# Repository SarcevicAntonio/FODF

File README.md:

# Fundamentals of Digital Fabrication

This repo is the documentation of my Fundamentals of Digital Fabrication class, where we learned about the basics of 2D and 3D Design, Laser Cutting, 3D Printing, Electronics Productions and Design and Embedded Programming with Input and Output Devices. We then had to use all these skills in a Final Project.

[Read more in the documentation of the class.](https://sarcevicantonio.github.io/FODF/)

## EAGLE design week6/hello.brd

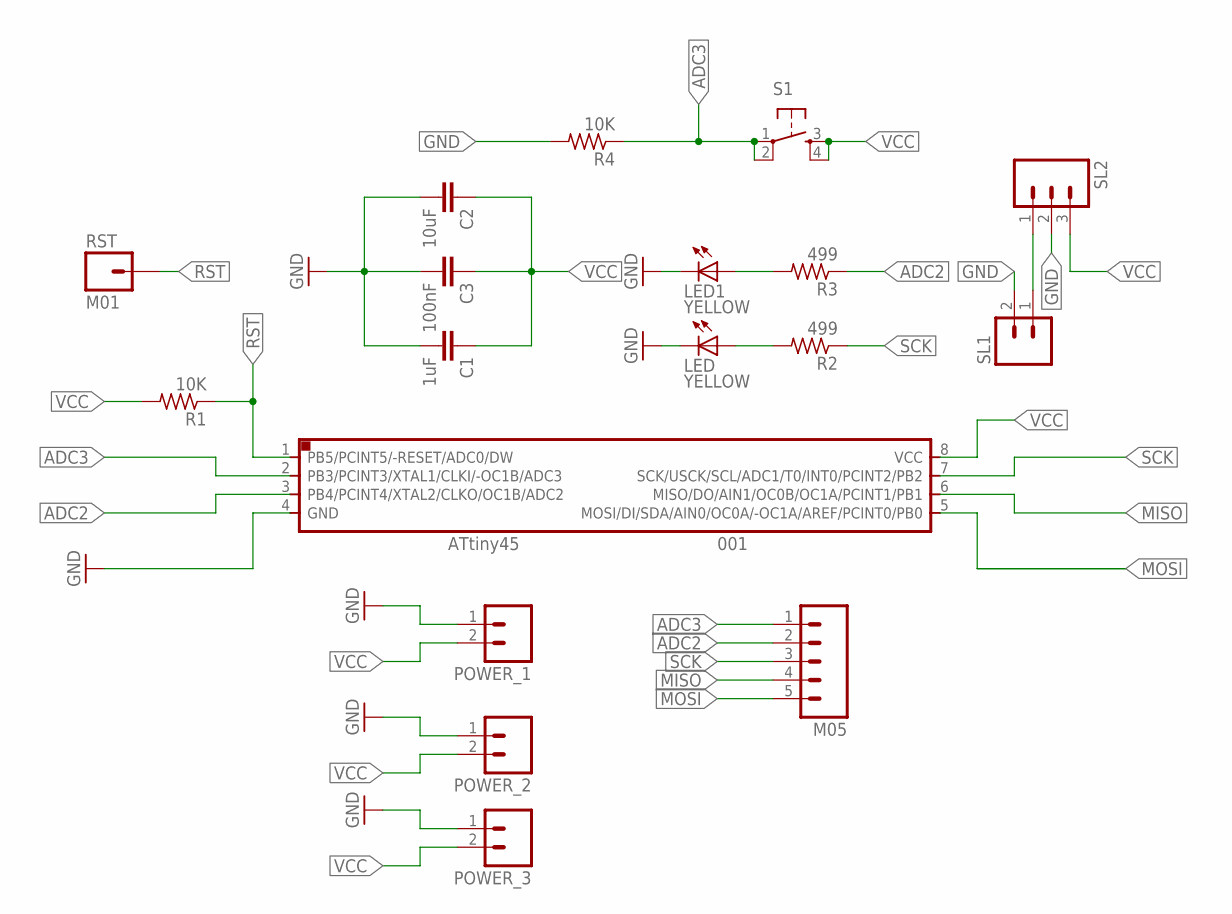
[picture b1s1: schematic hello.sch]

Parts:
001: ATTINY45SI; SOIC8
C1: 1uF; 1206
C2: 10uF; 1206
C3: 100nF; 1206
LED, LED1: YELLOW; LED1206FAB
M05: M05; 05P
POWER_1, POWER_2, POWER_3: M02; 02P
R1, R4: 10K; R1206FAB
R2, R3: 499; R1206FAB
RST: M01; 1X01_LONGPAD
S1: 6MM_SWITCH6MM_SWITCH; 6MM_SWITCH
SL1: M02; 02P
SL2: M03; 03P

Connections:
ADC2: 001.3 (PB4/PCINT4/XTAL2/CLKO/OC1B/ADC2), M05.2, R3.1
ADC3: 001.2 (PB3/PCINT3/XTAL1/CLKI/-OC1B/ADC3), M05.1, R4.1, S1.1, S1.2 (P1)
GND: 001.4 (GND), C1.2, C2.2, C3.2, LED.2 (C), LED1.2 (C), POWER_1.1, POWER_2.1, POWER_3.1, R4.2, SL1.2, SL2.2
MISO: 001.6 (MISO/DO/AIN1/OC0B/OC1A/PCINT1/PB1), M05.4
MOSI: 001.5 (MOSI/DI/SDA/AIN0/OC0A/-OC1A/AREF/PCINT0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), M05.5
unnamed: LED1.1 (A), R3.2
unnamed: SL1.1, SL2.1
unnamed: LED.1 (A), R2.2
RST: 001.1 (PB5/PCINT5/-RESET/ADC0/DW), R1.1, RST.1
SCK: 001.7 (SCK/USCK/SCL/ADC1/T0/INT0/PCINT2/PB2), M05.3, R2.1
VCC: 001.8 (VCC), C1.1, C2.1, C3.1, POWER_1.2, POWER_2.2, POWER_3.2, R1.2, S1.3 (S), S1.4 (S1), SL2.3

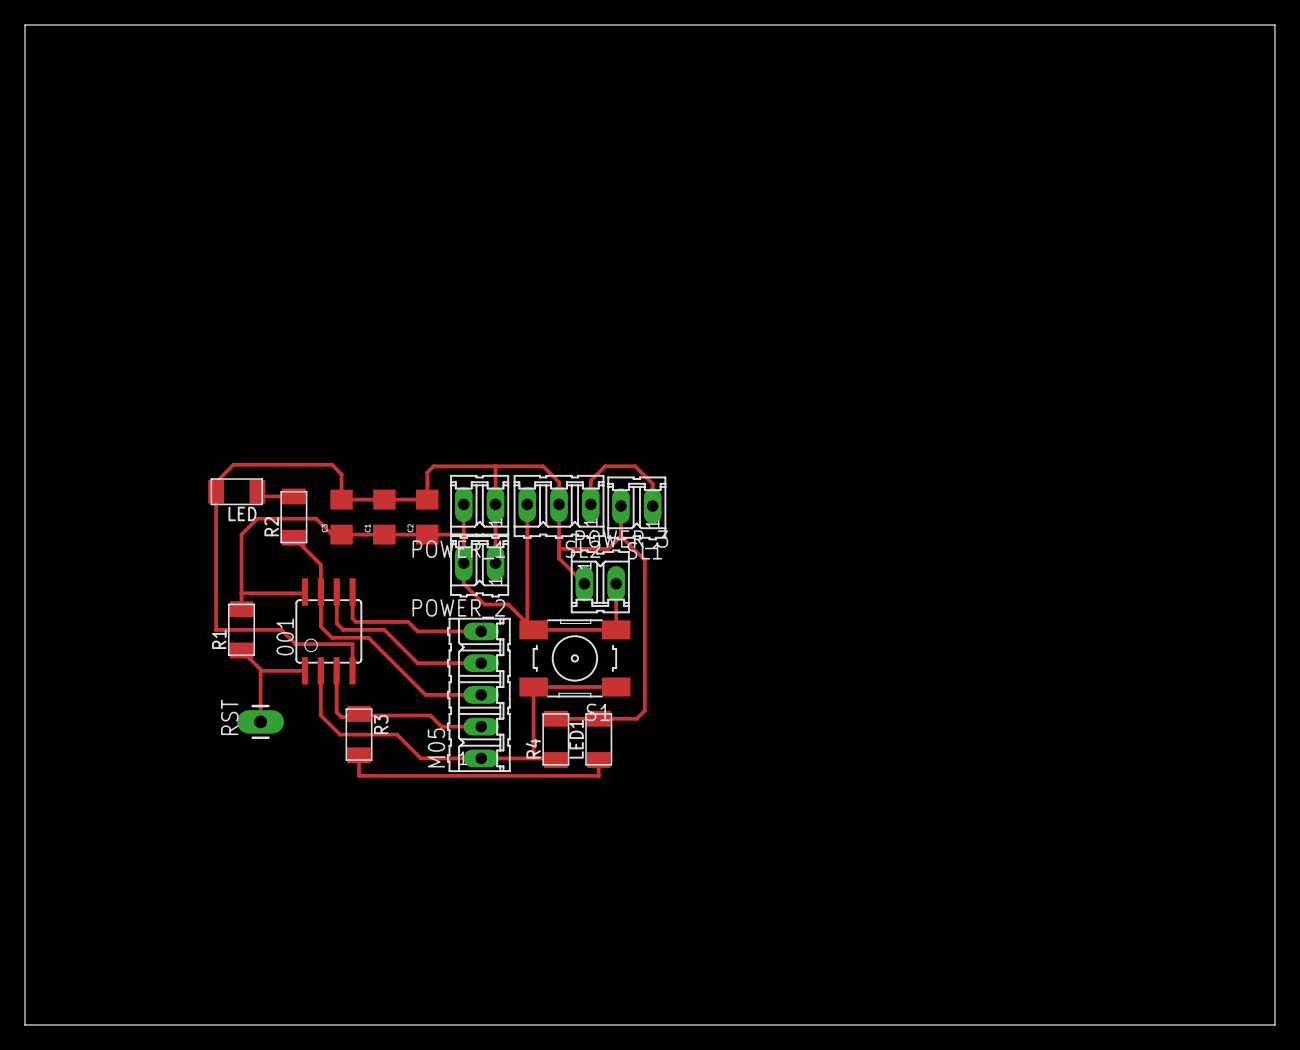
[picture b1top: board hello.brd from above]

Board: 2 copper layers, 100.0 x 80.0 mm, 18 parts (0 on the bottom side), 11 nets.

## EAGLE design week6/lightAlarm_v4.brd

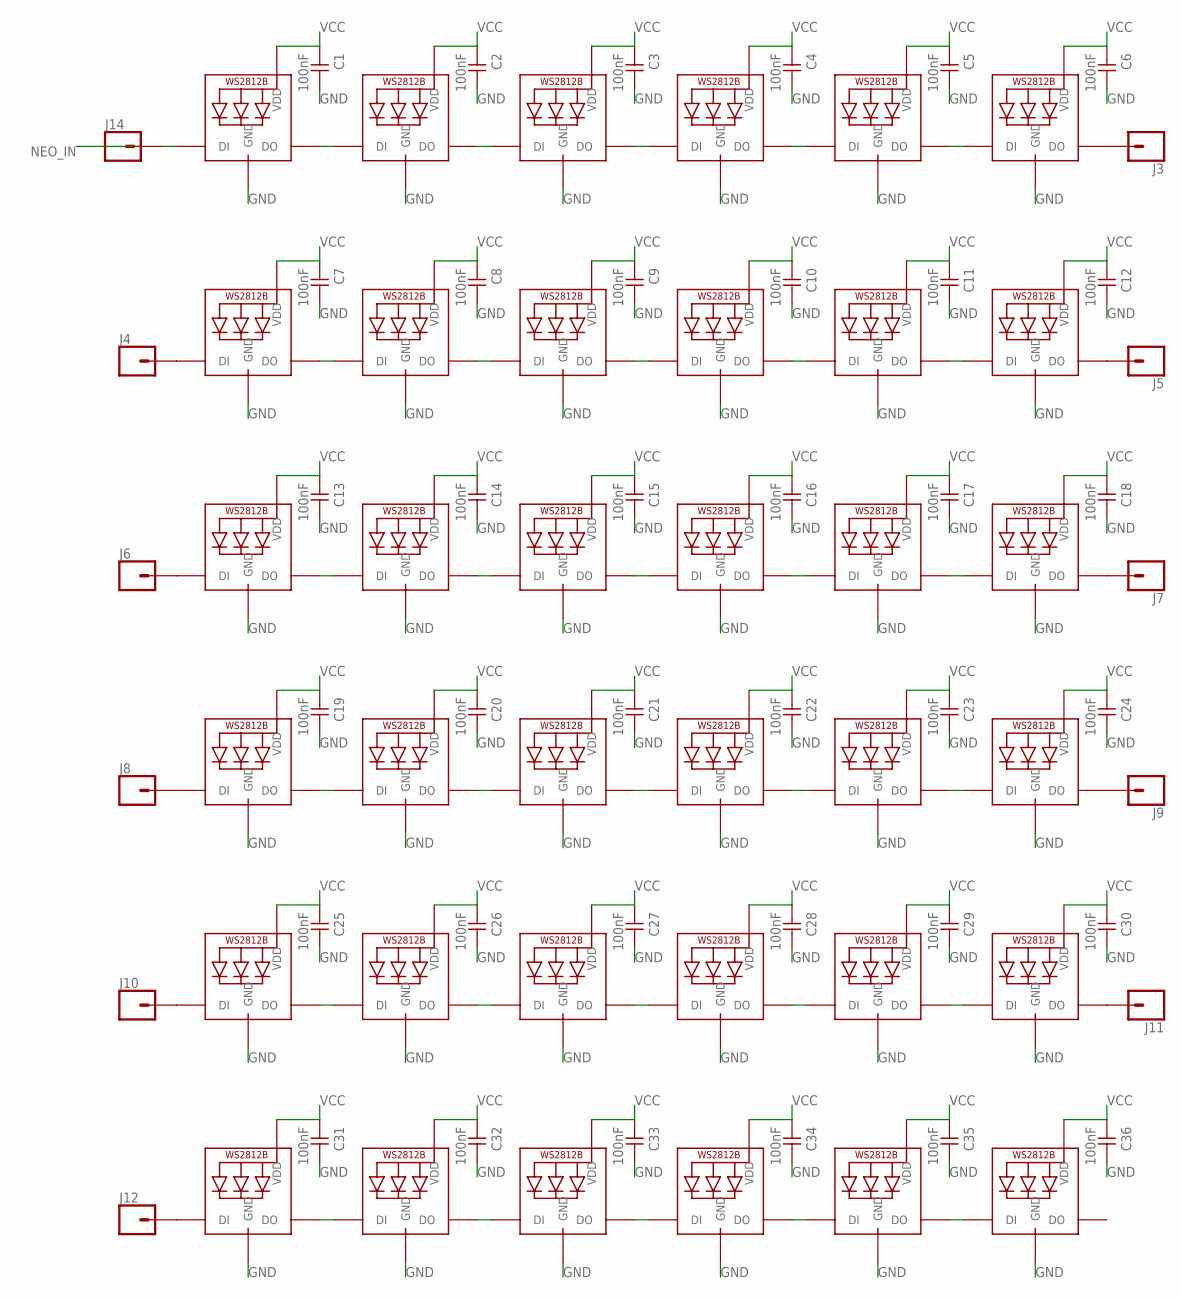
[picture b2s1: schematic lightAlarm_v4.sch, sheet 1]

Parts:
C1, C2, C3, C4, C5, C6, C7, C8, C9, C10, C11, C12, C13, C14, C15, C16, C17, C18, C19, C20, C21, C22, C23, C24, C25, C26, C27, C28, C29, C30, C31, C32, C33, C34, C35, C36: 100nF; 1206
J3, J4, J5, J6, J7, J8, J9, J10, J11, J12, J14: CONN_01PTH_LONGPAD; 1X01_LONGPAD
LED1, LED2, LED3, LED4, LED5, LED6, LED7, LED8, LED9, LED10, LED11, LED12, LED13, LED14, LED15, LED16, LED17, LED18, LED19, LED20, LED21, LED22, LED23, LED24, LED25, LED26, LED27, LED28, LED29, LED30, LED31, LED32, LED33, LED34, LED35, LED36: WS2812B5050; WS2812B

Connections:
GND: C1.2, C2.2, C3.2, C4.2, C5.2, C6.2, C7.2, C8.2, C9.2, C10.2, C11.2, C12.2, C13.2, C14.2, C15.2, C16.2, C17.2, C18.2, C19.2, C20.2, C21.2, C22.2, C23.2, C24.2, C25.2, C26.2, C27.2, C28.2, C29.2, C30.2, C31.2, C32.2, C33.2, C34.2, C35.2, C36.2, LED1.3-GND (GND), LED2.3-GND (GND), LED3.3-GND (GND), LED4.3-GND (GND), LED5.3-GND (GND), LED6.3-GND (GND), LED7.3-GND (GND), LED8.3-GND (GND), LED9.3-GND (GND), LED10.3-GND (GND), LED11.3-GND (GND), LED12.3-GND (GND), LED13.3-GND (GND), LED14.3-GND (GND), LED15.3-GND (GND), LED16.3-GND (GND), LED17.3-GND (GND), LED18.3-GND (GND), LED19.3-GND (GND), LED20.3-GND (GND), LED21.3-GND (GND), LED22.3-GND (GND), LED23.3-GND (GND), LED24.3-GND (GND), LED25.3-GND (GND), LED26.3-GND (GND), LED27.3-GND (GND), LED28.3-GND (GND), LED29.3-GND (GND), LED30.3-GND (GND), LED31.3-GND (GND), LED32.3-GND (GND), LED33.3-GND (GND), LED34.3-GND (GND), LED35.3-GND (GND), LED36.3-GND (GND); also elsewhere on the board
unnamed: LED1.2-DOUT (DO), LED2.4-DIN (DI)
unnamed: LED3.2-DOUT (DO), LED4.4-DIN (DI)
unnamed: LED2.2-DOUT (DO), LED3.4-DIN (DI)
unnamed: LED5.2-DOUT (DO), LED6.4-DIN (DI)
unnamed: LED4.2-DOUT (DO), LED5.4-DIN (DI)
unnamed: LED7.2-DOUT (DO), LED8.4-DIN (DI)
unnamed: LED9.2-DOUT (DO), LED10.4-DIN (DI)
unnamed: LED8.2-DOUT (DO), LED9.4-DIN (DI)
unnamed: LED11.2-DOUT (DO), LED12.4-DIN (DI)
unnamed: LED10.2-DOUT (DO), LED11.4-DIN (DI)
unnamed: LED13.2-DOUT (DO), LED14.4-DIN (DI)
unnamed: LED15.2-DOUT (DO), LED16.4-DIN (DI)
unnamed: LED14.2-DOUT (DO), LED15.4-DIN (DI)
unnamed: LED17.2-DOUT (DO), LED18.4-DIN (DI)
unnamed: LED16.2-DOUT (DO), LED17.4-DIN (DI)
unnamed: LED19.2-DOUT (DO), LED20.4-DIN (DI)
unnamed: LED21.2-DOUT (DO), LED22.4-DIN (DI)
unnamed: LED20.2-DOUT (DO), LED21.4-DIN (DI)
unnamed: LED23.2-DOUT (DO), LED24.4-DIN (DI)
unnamed: LED22.2-DOUT (DO), LED23.4-DIN (DI)
unnamed: LED25.2-DOUT (DO), LED26.4-DIN (DI)
unnamed: LED27.2-DOUT (DO), LED28.4-DIN (DI)
unnamed: LED26.2-DOUT (DO), LED27.4-DIN (DI)
unnamed: LED29.2-DOUT (DO), LED30.4-DIN (DI)
unnamed: LED28.2-DOUT (DO), LED29.4-DIN (DI)
unnamed: LED31.2-DOUT (DO), LED32.4-DIN (DI)
unnamed: LED33.2-DOUT (DO), LED34.4-DIN (DI)
unnamed: LED32.2-DOUT (DO), LED33.4-DIN (DI)
unnamed: LED35.2-DOUT (DO), LED36.4-DIN (DI)
unnamed: LED34.2-DOUT (DO), LED35.4-DIN (DI)
unnamed: J3.1, LED6.2-DOUT (DO)
unnamed: J5.1, LED12.2-DOUT (DO)
unnamed: J6.1, LED13.4-DIN (DI)
unnamed: J7.1, LED18.2-DOUT (DO)
unnamed: J8.1, LED19.4-DIN (DI)
unnamed: J9.1, LED24.2-DOUT (DO)
unnamed: J10.1, LED25.4-DIN (DI)
unnamed: J11.1, LED30.2-DOUT (DO)
unnamed: J12.1, LED31.4-DIN (DI)
unnamed: J14.1, LED1.4-DIN (DI)
ROW1: J4.1, LED7.4-DIN (DI)
VCC: C1.1, C2.1, C3.1, C4.1, C5.1, C6.1, C7.1, C8.1, C9.1, C10.1, C11.1, C12.1, C13.1, C14.1, C15.1, C16.1, C17.1, C18.1, C19.1, C20.1, C21.1, C22.1, C23.1, C24.1, C25.1, C26.1, C27.1, C28.1, C29.1, C30.1, C31.1, C32.1, C33.1, C34.1, C35.1, C36.1, LED1.1-VDD (VDD), LED2.1-VDD (VDD), LED3.1-VDD (VDD), LED4.1-VDD (VDD), LED5.1-VDD (VDD), LED6.1-VDD (VDD), LED7.1-VDD (VDD), LED8.1-VDD (VDD), LED9.1-VDD (VDD), LED10.1-VDD (VDD), LED11.1-VDD (VDD), LED12.1-VDD (VDD), LED13.1-VDD (VDD), LED14.1-VDD (VDD), LED15.1-VDD (VDD), LED16.1-VDD (VDD), LED17.1-VDD (VDD), LED18.1-VDD (VDD), LED19.1-VDD (VDD), LED20.1-VDD (VDD), LED21.1-VDD (VDD), LED22.1-VDD (VDD), LED23.1-VDD (VDD), LED24.1-VDD (VDD), LED25.1-VDD (VDD), LED26.1-VDD (VDD), LED27.1-VDD (VDD), LED28.1-VDD (VDD), LED29.1-VDD (VDD), LED30.1-VDD (VDD), LED31.1-VDD (VDD), LED32.1-VDD (VDD), LED33.1-VDD (VDD), LED34.1-VDD (VDD), LED35.1-VDD (VDD), LED36.1-VDD (VDD); also elsewhere on the board

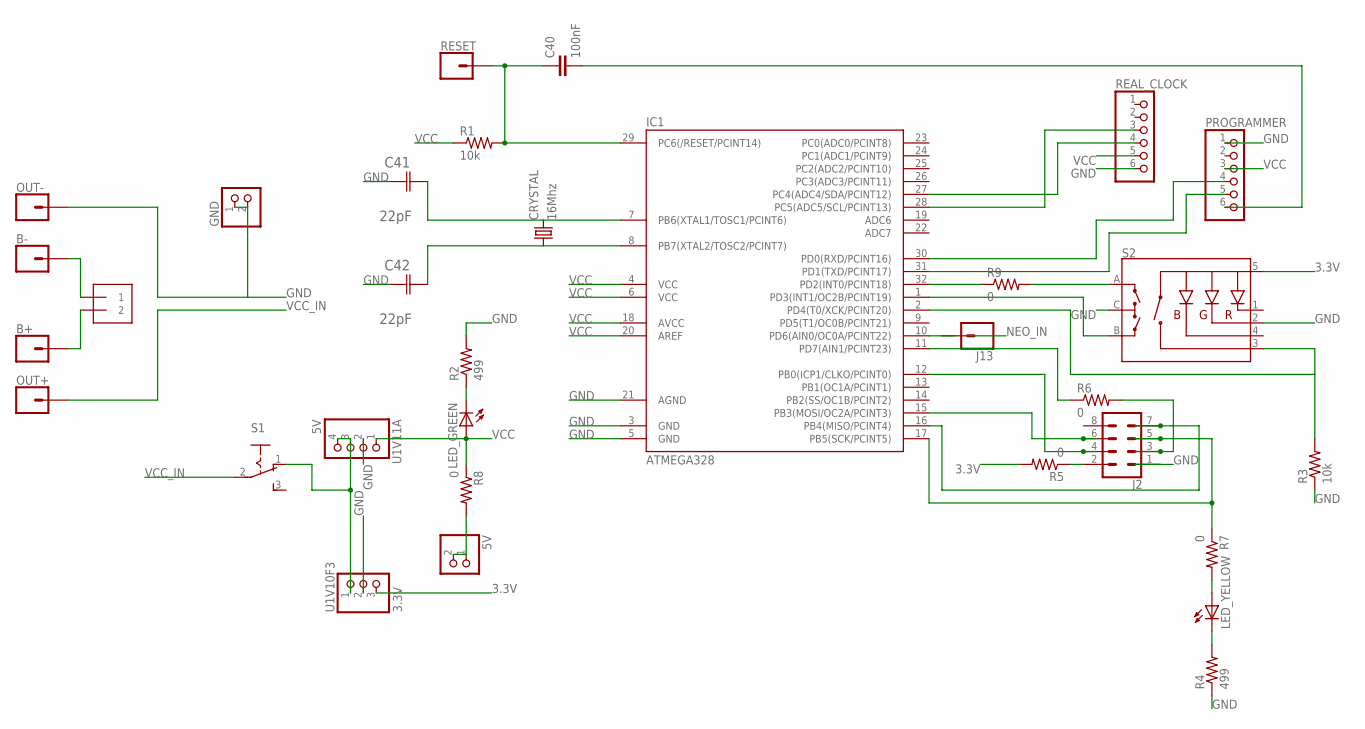
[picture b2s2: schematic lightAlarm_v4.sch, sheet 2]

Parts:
5V: PINHD-1X2; 1X02
B+: CONN_01PTH_LONGPAD; 1X01_LONGPAD
B-: CONN_01PTH_LONGPAD; 1X01_LONGPAD
C40: 100nF; 1206
C41, C42: 22pF; CAPC3216X178N
CRYSTAL: 16Mhz; CSM-7X-DU
GND: PINHD-1X2; 1X02
IC1: ATMEGA328; TQFP32-08
J1: 1X2-3.5MM
J2: CONN_04X2; 2X4
J13: CONN_01PTH_LONGPAD; 1X01_LONGPAD
LED_GREEN: LED1206; 1206
LED_YELLOW: LED1206; 1206
OUT+: CONN_01PTH_LONGPAD; 1X01_LONGPAD
OUT-: CONN_01PTH_LONGPAD; 1X01_LONGPAD
PROGRAMMER: PINHD-1X6; 1X06
R1, R3: 10k; 1206
R2, R4: 499; 1206
R5, R6, R7, R8, R9: 0; 1206
REAL_CLOCK: PINHD-1X6; 1X06
RESET: CONN_01PTH_LONGPAD; 1X01_LONGPAD
S1: 255SB
S2: ENCODER-RGB-SWITCH; ENCODER_LED_3
U1V10F3: 3.3V; 1X03
U1V11A: 5V; 1X04

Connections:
3.3V: J2.2, R5.1, R5.2, S2.5 (+), U1V10F3.3
GND: C41.1 (C1), C42.1 (C1), GND.1, GND.2, IC1.3 (GND), IC1.5 (GND), IC1.21 (AGND), J2.1, OUT-.1, PROGRAMMER.1, R2.2, R3.1, R4.1, REAL_CLOCK.6, S2.2 (-G), S2.C, U1V10F3.2, U1V11A.2; also elsewhere on the board
unnamed: B+.1, J1.2
unnamed: LED_GREEN.2 (C), R2.1
unnamed: S1.1 (O), U1V10F3.1, U1V11A.3, U1V11A.4
unnamed: C41.2 (C2), CRYSTAL.2, IC1.7 (PB6(XTAL1/TOSC1/PCINT6))
unnamed: C42.2 (C2), CRYSTAL.1, IC1.8 (PB7(XTAL2/TOSC2/PCINT7))
unnamed: IC1.11 (PD7(AIN1/PCINT23)), R6.1
unnamed: IC1.12 (PB0(ICP1/CLKO/PCINT0)), J2.4
unnamed: IC1.17 (PB5(SCK/PCINT5)), J2.5, LED_YELLOW.1 (A), R7.1, R7.2
unnamed: IC1.15 (PB3(MOSI/OC2A/PCINT3)), J2.6
unnamed: IC1.16 (PB4(MISO/PCINT4)), J2.7
unnamed: B-.1, J1.1
unnamed: IC1.27 (PC4(ADC4/SDA/PCINT12)), REAL_CLOCK.4
unnamed: IC1.28 (PC5(ADC5/SCL/PCINT13)), REAL_CLOCK.3
unnamed: IC1.30 (PD0(RXD/PCINT16)), PROGRAMMER.4
unnamed: IC1.31 (PD1(TXD/PCINT17)), PROGRAMMER.5
unnamed: IC1.32 (PD2(INT0/PCINT18)), R9.1, R9.2, S2.A
unnamed: IC1.1 (PD3(INT1/OC2B/PCINT19)), S2.B
unnamed: IC1.2 (PD4(T0/XCK/PCINT20)), R3.2, S2.3 (SW)
unnamed: LED_YELLOW.2 (C), R4.2
unnamed: J2.3, R6.2
unnamed: C40.1, R1.2, RESET.1
unnamed: C40.2, PROGRAMMER.6
unnamed: IC1.10 (PD6(AIN0/OC0A/PCINT22)), J13.1
VCC: 5V.1, 5V.2, IC1.4 (VCC), IC1.6 (VCC), LED_GREEN.1 (A), PROGRAMMER.3, R1.1, R8.1, R8.2, REAL_CLOCK.5, U1V11A.1; also elsewhere on the board
VCC_IN: OUT+.1, S1.2

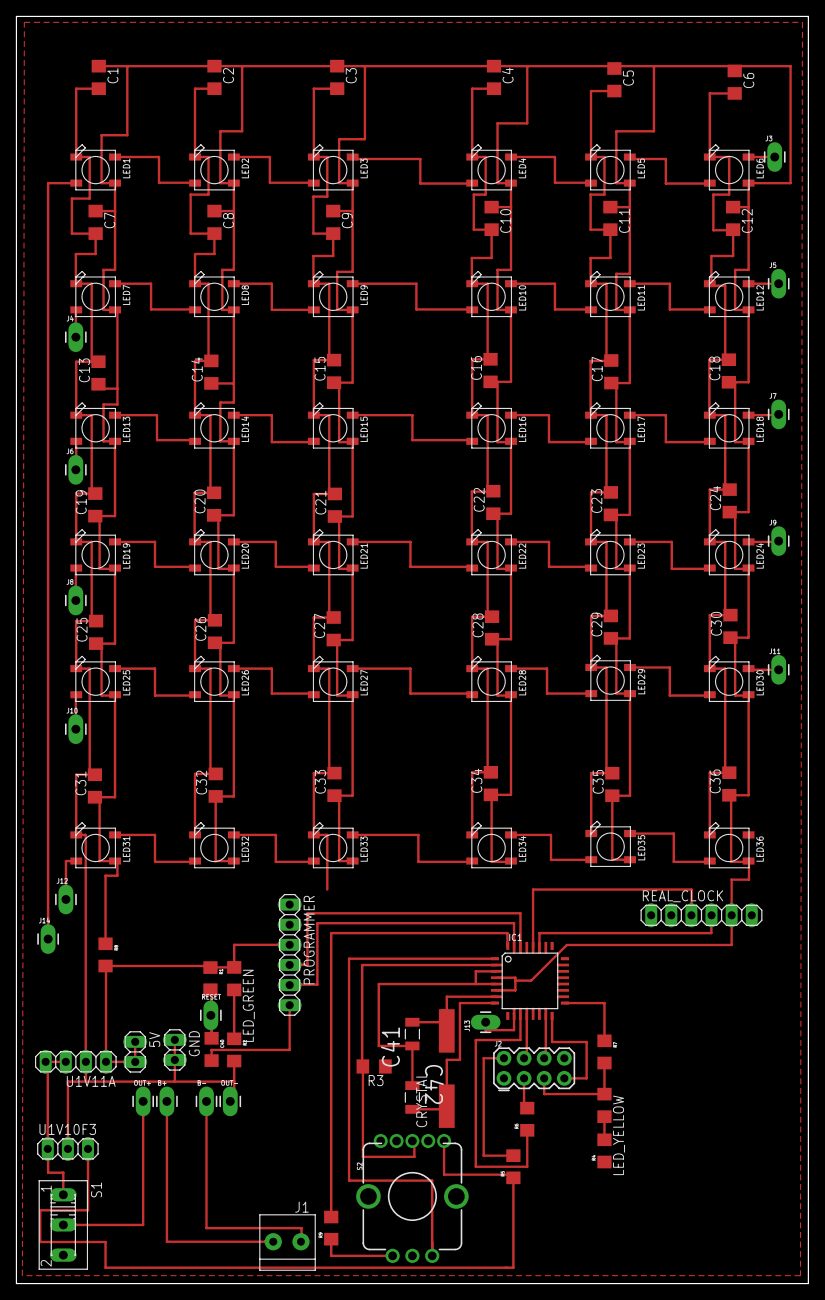
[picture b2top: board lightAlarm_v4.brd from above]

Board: 2 copper layers, 100.0 x 160.0 mm, 115 parts (0 on the bottom side), 68 nets.

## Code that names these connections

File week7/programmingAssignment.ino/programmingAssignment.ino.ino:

#include <SoftwareSerial.h>               //Including the SoftwareSerial library
#define RX PB0                            //Defining the MOSI Pin as RX
#define TX PB1                            //Defining the MISO Pin as TX
SoftwareSerial mySerial(RX, TX);          //Defining the SoftwareSerial Pins (RX, TX)

#define LED_PIN1 PB2                      //Define LED 1 Pin to PB2
#define LED_PIN2 PB4                      //Define LED 2 Pin to PB4

#define BUTTON_PIN PB3                    //Define Button Pin to BP3
int buttonState = false;                  //Variable for the state of the Button
 
char message[18] = "this is a for loop";  //Message as character array

void setup() {  
  pinMode(LED_PIN1, OUTPUT);              //LED 1 as OUTPUT
  pinMode(LED_PIN2, OUTPUT);              //LED 2 as OUTPUT
  pinMode(BUTTON_PIN, INPUT);             //BUTTON as INPUT
  mySerial.begin(2400);                   //Opening the serial, 2400 as data rate
  for(int i = 0; i < 18; i++){            //for loop, i will go from 0 to 18 in steps of 1
    mySerial.print(message[i]);           //Print character of array from current position of i
    delay(10);                            //Wait a bit
  }
}

void loop() {
  buttonState = digitalRead(BUTTON_PIN);  //Read the state of the button at the begining of the loop
  if(buttonState ==  HIGH){               //Code below will run, when the button is pressed
    turnBothLedOn();                      //Calls function to turn on both LEDs
    mySerial.println("Button is being pressed!"); //Writes button state in serial
  }else{                                  //Code below will run, when button is not pressed
    turnBothLedOff();                     //Calls function to turn off both LEDs
    mySerial.println("Button NOT is being pressed!"); //Writes button state in Serial
  }
  delay(100);                             //Wait a bit, to not spam the serial too much
}

void turnBothLedOn() {
    digitalWrite(LED_PIN1, HIGH);         //Turn the LED1 on   
    digitalWrite(LED_PIN2, HIGH);         //Turn the LED2 on
}

void turnBothLedOff() {
    digitalWrite(LED_PIN1, LOW);          //Turn the LED1 off
    digitalWrite(LED_PIN2, LOW);          //Turn the LED2 off
}

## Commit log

2021-09-18 uploaded documentation

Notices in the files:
parts and their libraries:
01_SparkFun: Licensing: CC v3.0 Share-Alike You are welcome to use this library for commercial purposes.
SparkFun-Switches: Licensing: Creative Commons ShareAlike 4.0 International - https://creativecommons.org/licenses/by-sa/4.0
